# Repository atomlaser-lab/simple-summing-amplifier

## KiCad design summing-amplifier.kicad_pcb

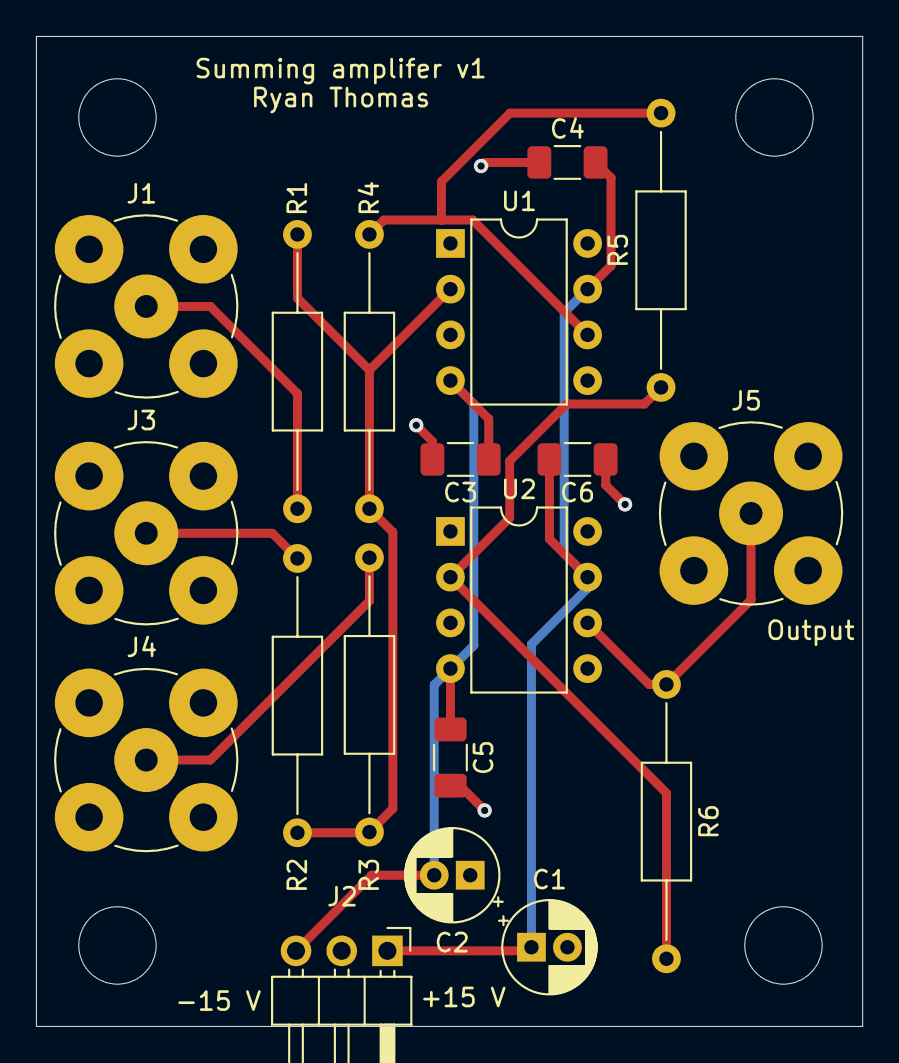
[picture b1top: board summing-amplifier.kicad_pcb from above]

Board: 2 copper layers, 45.9 x 55.0 mm, 19 parts (0 on the bottom side), 10 nets.

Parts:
C1, C2: CP; CP_Radial_D5.0mm_P2.00mm
C3, C4, C5, C6: 100n; C_1206_3216Metric_Pad1.33x1.80mm_HandSolder
J1, J3, J4, J5: Conn_Coaxial; BNC_TEConnectivity_1478204_Vertical
J2: Conn_01x03_Male; PinHeader_1x03_P2.54mm_Horizontal
R1, R2, R3, R4, R5, R6: 10k; R_Axial_DIN0207_L6.3mm_D2.5mm_P15.24mm_Horizontal
U1, U2: LM318N; DIP-8_W7.62mm

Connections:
/VDD: C1.1, C4.2, C6.2, J2.1, U1.7, U2.7
/VSS: C2.2, C3.1, C5.1, J2.3, U1.4, U2.4
GND: C1.2, C2.1, C3.2, C4.1, C5.2, C6.1, J1.2, J2.2, J3.2, J4.2, J5.2, U1.3, U2.3
unnamed: J1.1, R1.2
unnamed: J3.1, R2.2
unnamed: J4.1, R3.2
unnamed: J5.1, R6.1, U2.6
unnamed: R1.1, R2.1, R3.1, R4.2, U1.2
unnamed: R4.1, R5.2, U1.6
unnamed: R5.1, R6.2, U2.2

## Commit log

2022-09-29 Initial commit, production
